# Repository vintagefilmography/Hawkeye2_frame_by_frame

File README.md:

# Hawkeye2_frame_by_frame
The purpose of this project is to prvide the instruction to the user on how to modify the existing 8mm film projector for the frame-byframe capture directly into the camera using a small MSP430 based board.  
Generally the projects of this type require several modifications to the projector including the light change, motor change and addition of some type of a trigger detector for the camera.  
This project also requires the light change and the motor change, but unlike similar other projects, it does not require the trigger mechanism. The trigger is pprovided by the MSP430 controller. The controller is programmed to precisely control the stepper motor rotation so that the film gets advanced exactly one frame at the time. The camera trigger is then generated at the end of frame advance.  

System Components

## Hawkeye2 Controller  
At the heart of the system is the Hawkeye2 controller. This is a custom design. All design info is available gere is this repository. The board details are included in  the homemade-v3 folder. Download the folder to your Eagle project directory and there you will have access to the schematic and the board layout. 
The MSP430 micro controller firmware is available in the MSP folder. Download the zip file from there and save it in you TI Code Composer project directory. From there you can edit the source and flash the target by using TI Launchpad.  
There are two more boards included. One is for the front panel switches and the other is for the switch interface board. Follow the included wiring diagram to interconnect the system.
## Stepper Driver  
The stepper driver is an off the shelf product. 
https://www.amazon.com/gp/product/B075HBJP51/
There are many other variants available. This particular one is a good choice because it has 256 micro steps allowing for a very precise tuning control. One disadvantage is that it operates from a 24VDC source so that 2 DC adaprers are required, one for the driver and the other one for the controller that requires 12VDC source.  
Driver dip switches  
The following is recommended:
SW4 - Half Currect
Current - 
1.4A for this type motor https://www.amazon.com/gp/product/B00PNEQKC0/
2.7A for this type motor https://www.amazon.com/gp/product/B00PNEPF5I/
Set the pulse/rev switches for the highest speed that can still hold the torque and there is no skipping of steps. Skipping will result in loss of synchronization.  
## Stepper Motor  
These two motors were tested.
1.4A for this type motor https://www.amazon.com/gp/product/B00PNEQKCdesigned with Spark0/
2.7A for this type motor https://www.amazon.com/gp/product/B00PNEPF5I/
You will have to design a bracket for the motor so that it fits properly in the projector after you remove the old motor. 
A sample stepper bracket is included here as a good staring point. Use the Designspark Mechanical free software to modify the bracket for your projector.

## Pulley
There are quite a few pulleys avaliable online.  
Example:  
https://www.amazon.com/gp/product/B07C4R3PGV/  
https://www.amazon.com/gp/product/B07C4QD1BV/
You can also design your own. A sample design will be included here shortly.

## Belt
This used to be a big problem but with the neophrene Urethane belting that became available it is easy to make your own custom belt.
https://www.amazon.com/gp/product/B07L3W7Z1N  
Follow the following instructions:  
https://www.youtube.com/watch?v=mBtHvPWVgDw

## Control Switches:

The control switches control the operation of the unit.  
### RUN Switch
Pauses the operation  
### ALIGN
Slowly advances the film until the frame is centered in the camera. Also turns tuning on if activated in run mode.  
### REW
Turns takeup continuously on if run switch is off.  
The switch can also be used in conjuction with the PROJ switch to select the projector type. 
I.e. if the setup is used with multiple projectors then the projector synchronization can be saved in non volatile memory.  
Four memory locations are available:   
REW     PROJ  
0       0       Projector1  
0       1       Projector2  
1       0       Projector3  
1       1       Projector4  
The switches are active only during a short time after the power is plugged in and in most cases the only Projector1 selection will be used.  

### PROJ 
Seects the projector type used. In most cases this switch will be kept off. 
The projector selection is read by the firmware upon board power up and cannot be changed after that during normal operation.  
### UP and DOWN switches 
Used during tuning mode to run change the length of stepper advance.  
### Up and DOWN buttons
Located on the controller board, used for fine tuning of the stepper  
### REV Switch 
Reverses the motor rotation for film rewind.  

## Operation
Very straight forward. Here is a short video showing the operation.  
https://photos.app.goo.gl/MLEgviiinpVREHCQA  
As the video shows, plug the power in for both the controller and the driver and then flip the ADV switch on until the projector is finished with the film frame advance and at that point turn the ADV switch off. Then, connect the camera trigger and turn the camera on. Turn the RUn switch on the the camera will start capturing the farmes. If at any point the system starts goung out of sync you can resync it by using the ADV switch or alternatively, turn the ALG switch on and the hit the UP or DOWN button just once.   
The UP button makes the run shorter and the DOWN button makes it longer.  

## Tuning the Stepper  
Turn the RUN switch on. Make sure all other switches are off.

Turn the ALIGN switch on.  
This puts the controller into tuning mode.  
Turn on the DOWN switch. This makes the stepper step one count longer.  
While the DOWN switch is still on, turn on the UP switch.  
This will cause continuous stepper count increase. You will see that the film advance becomes larger and larger.   
After a while the stepper motor advance will  be close to one full turn of the projector cam.  
Once the alignment is close to a full cam rotation, turn the UP switch off and then the DOWN switch off.   
Continue with fine tuning by using the controller board mounted UP and DOWN buttons.  
The UP button will make the advance shorter by one count and conversely, the DOWN button will make it longer by one count.  
Once the alignment is done DO NOT POWER THE BOARD DOWN.  
Turn the ALIGN switch off and then the RUN switch off. Then you can power the board down.  
Power the board up again with the correct memory selected.
Turn the RUN switch on and check that the alignment was restored properly from the memory.  
It is to be noted that the UP and DOWN sequence can be reversed if the Film advance is too large.  
In that case turn the UP switch on first followed by the DOWN switch.   
Once done, turn the DOWN switch off first followed by the UP switch.

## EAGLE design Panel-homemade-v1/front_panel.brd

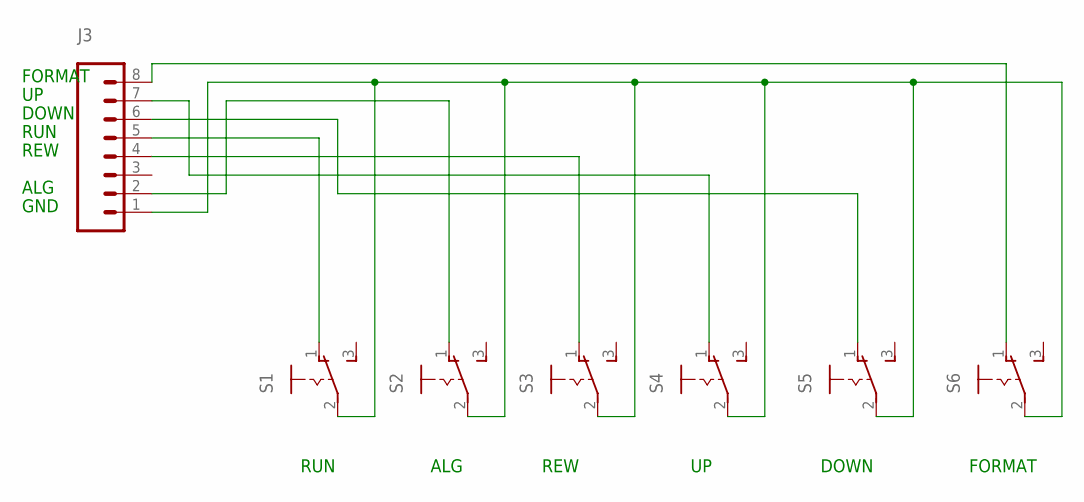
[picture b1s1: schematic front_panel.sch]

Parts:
J3: CONN_08"; 1X08
S1, S2, S3, S4, S5, S6: M251

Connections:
unnamed: J3.1, S1.2, S2.2, S3.2, S4.2, S5.2, S6.2
unnamed: J3.6, S5.1 (O)
unnamed: J3.4, S3.1 (O)
unnamed: J3.7, S4.1 (O)
unnamed: J3.2, S2.1 (O)
unnamed: J3.5, S1.1 (O)
unnamed: J3.8, S6.1 (O)

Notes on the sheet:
GND
ALG
REW
RUN
DOWN
FORMAT

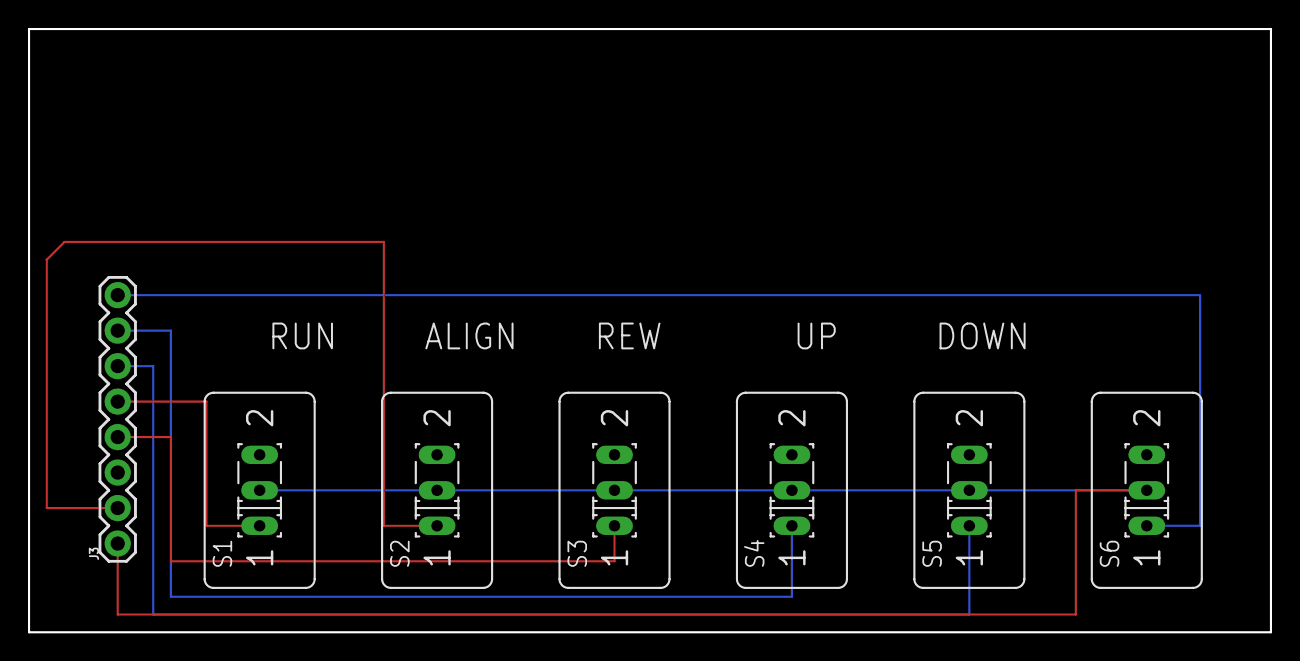
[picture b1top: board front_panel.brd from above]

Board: 2 copper layers, 88.9 x 43.2 mm, 7 parts (0 on the bottom side), 7 nets.

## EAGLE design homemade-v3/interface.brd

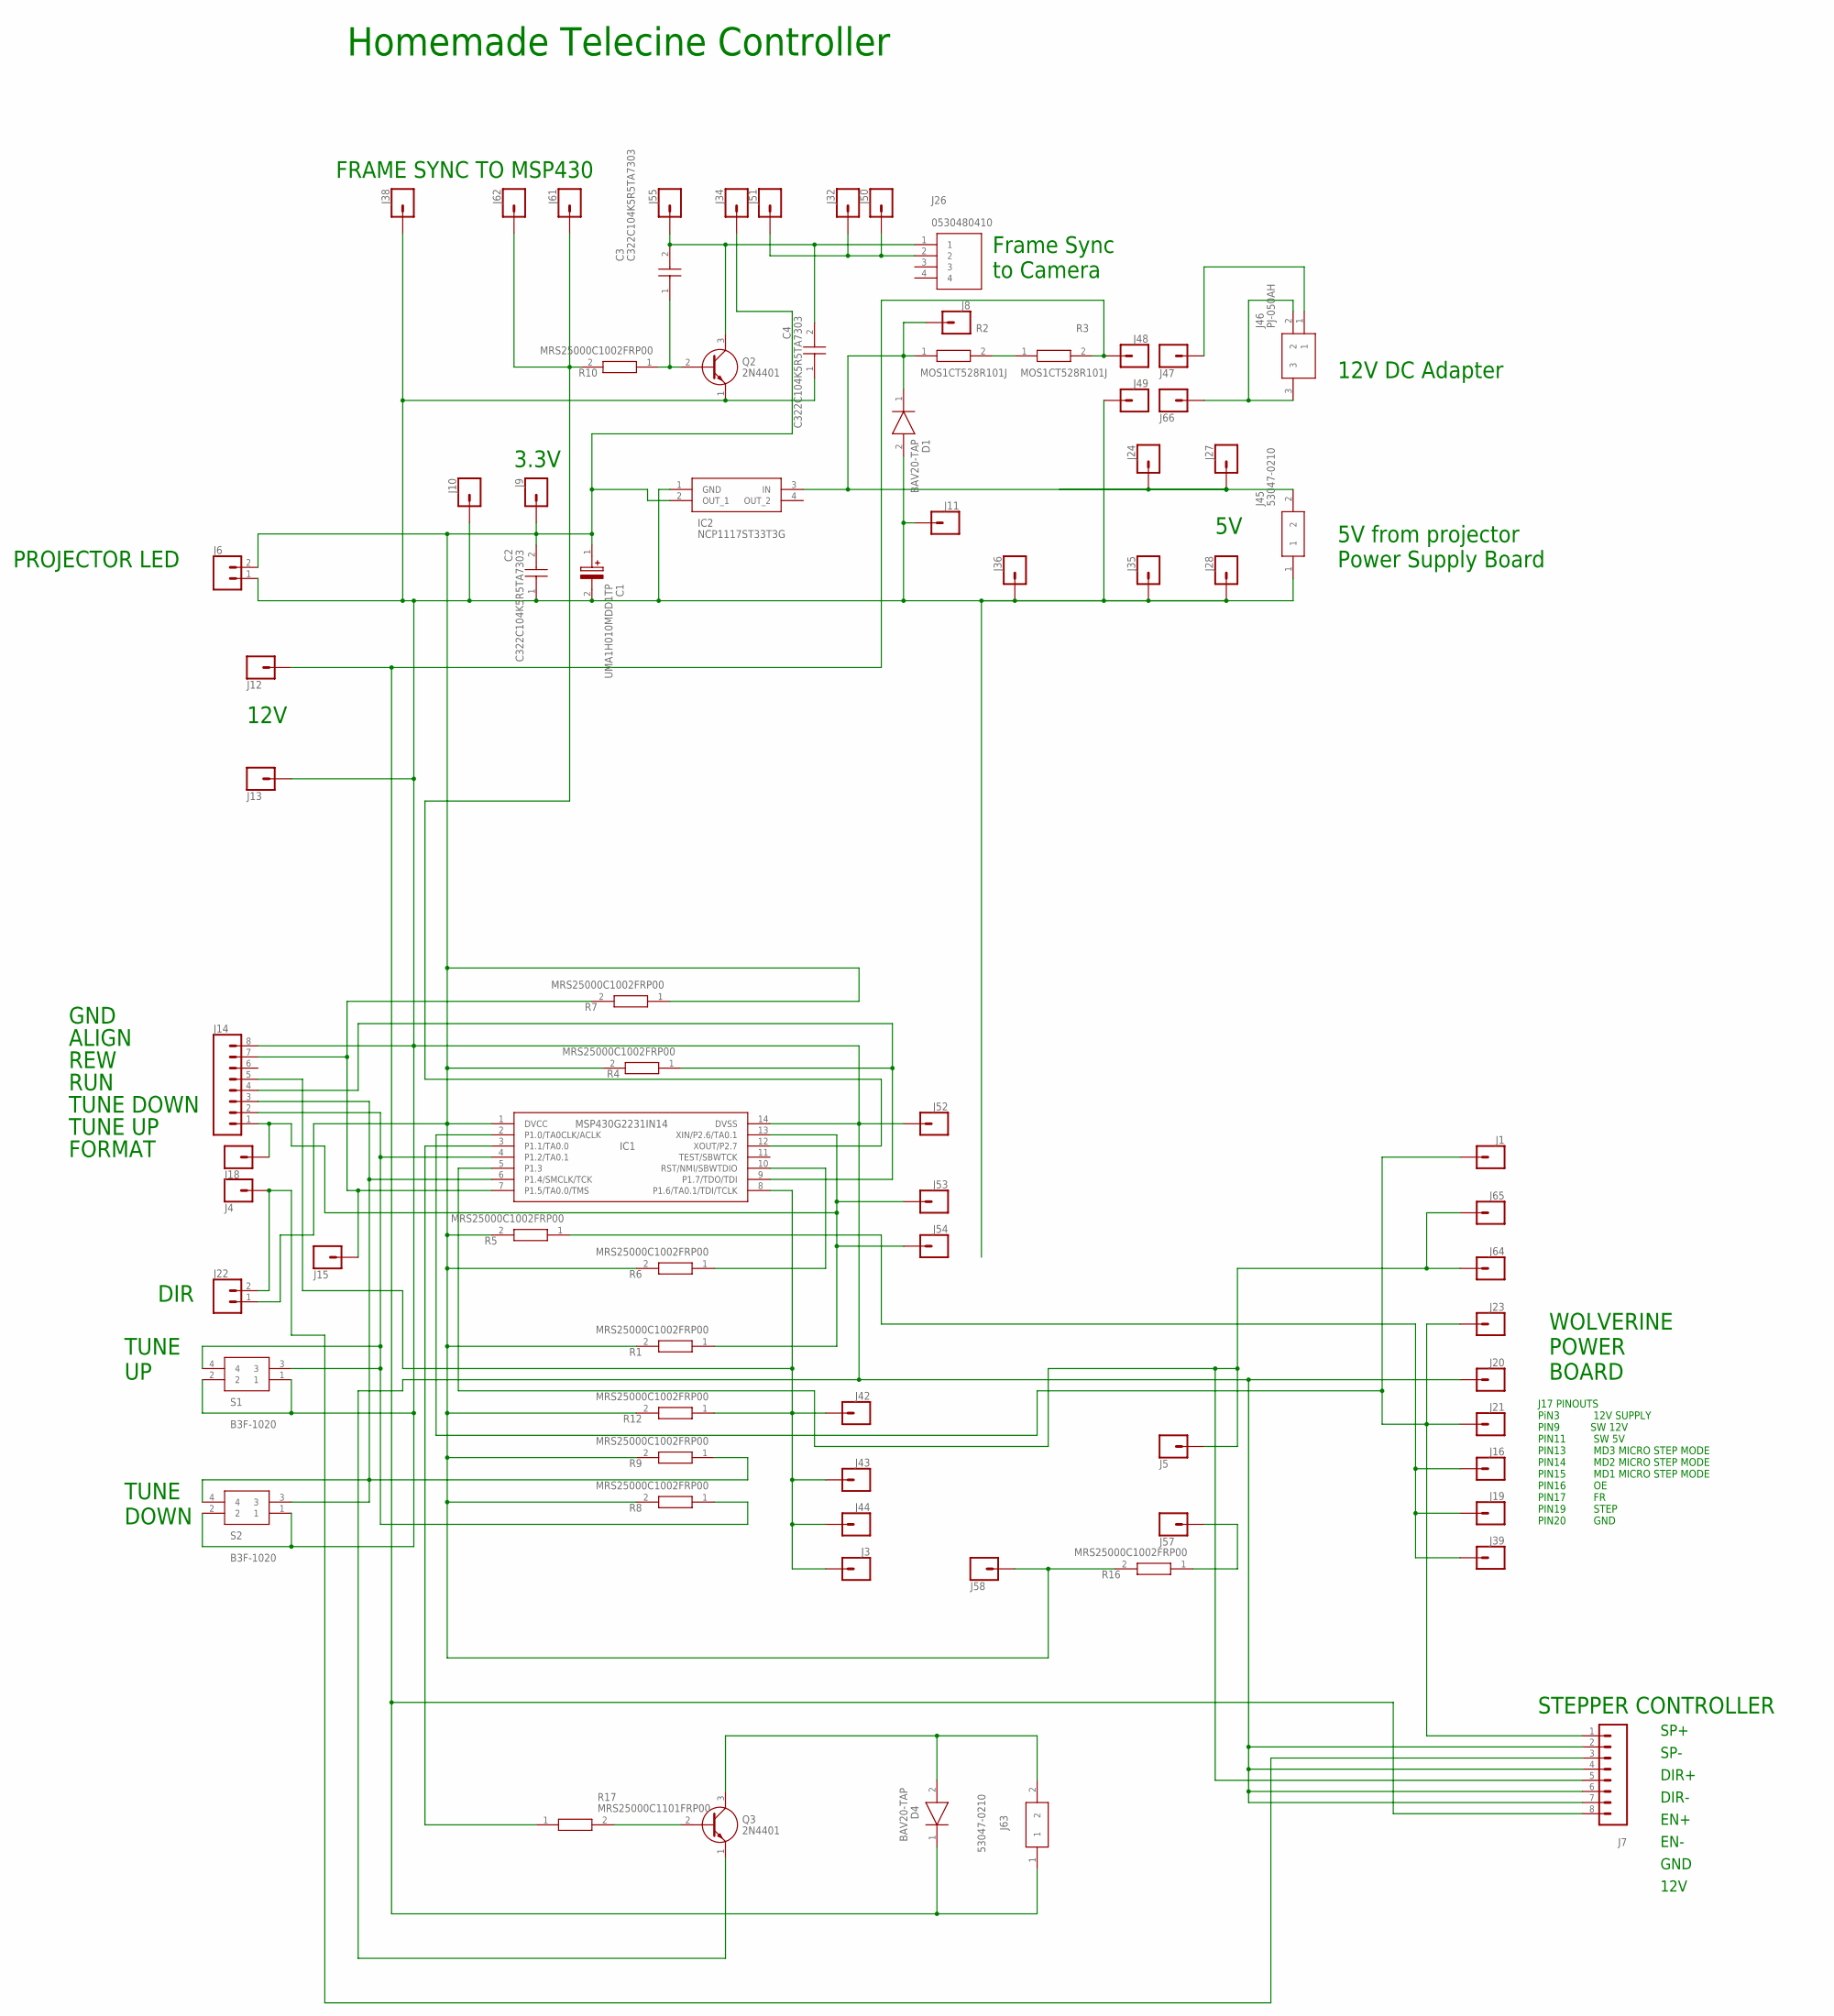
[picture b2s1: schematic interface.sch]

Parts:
C1: UMA1H010MDD1TP; CAPPRD150W45D450H600
C2, C3, C4: C322C104K5R5TA7303; C322
D1, D4: BAV20-TAP; DIOAD950W60L350D150
IC1: MSP430G2231IN14; DIP254P762X508-14
IC2: NCP1117ST33T3G; SOT230P700X180-4N
J1, J3, J4, J5, J8, J9, J10, J11, J12, J13, J15, J16, J18, J19, J20, J21, J23, J24, J27, J28, J32, J34, J35, J36, J38, J39, J42, J43, J44, J47, J48, J49, J50, J51, J52, J53, J54, J55, J57, J58, J61, J62, J64, J65, J66: CONN_01; 1X01
J6, J22: CONN_02; 1X02
J7, J14: CONN_08"; 1X08
J26: 0530480410; SHDR4W35P0X125_1X4_675X550X350
J45, J63: 53047-0210
J46: PJ-050AH; PJ050AH
Q2, Q3: 2N4401; CS_TO-92
R1, R4, R5, R6, R7, R8, R9, R10, R12, R16: MRS25000C1002FRP00; RESAD1650W60L650D250
R2, R3: MOS1CT528R101J; RESAD2100W60L900D300
R17: MRS25000C1101FRP00; RESAD1650W60L650D250
S1, S2: B3F-1020; B3F1000

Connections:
unnamed: C3.2, C4.2, J26.1, J55.1, Q2.3 (C)
unnamed: IC1.13 (XIN/P2.6/TA0.1), J14.1, J18.1, J53.1, J54.1, R1.1
unnamed: D4.1 (K), J7.8, J12.1, J48.1, J63.1, R3.2
unnamed: IC1.9 (P1.7/TDO/TDI), J14.4, R4.1
unnamed: J57.1, R16.1
unnamed: C1.1 (+), C2.2, IC1.1 (DVCC), IC2.2 (OUT_1), J6.2, J9.1, J22.1, J34.1, J58.1, R1.2, R4.2, R5.2, R6.2, R7.1, R8.2, R9.2, R12.2, R16.2
unnamed: IC1.3 (P1.1/TA0.0), R17.1
unnamed: IC1.10 (RST/NMI/SBWTDIO), R6.1
unnamed: R2.2, R3.1
unnamed: J4.1, J7.3, J22.2
unnamed: D1.1 (K), IC2.3 (IN), J8.1, J24.1, J27.1, J45.2, R2.1
unnamed: J46.1, J47.1
unnamed: IC1.7 (P1.5/TA0.0/TMS), J14.7, J15.1, R7.2
unnamed: J16.1, J19.1, J39.1, R5.1
unnamed: IC1.5 (P1.3), J5.1, J7.5, J64.1, J65.1
unnamed: IC1.2 (P1.0/TA0CLK/ACLK), J1.1, J7.1, J21.1, J23.1
unnamed: IC1.4 (P1.2/TA0.1), J14.2, R8.1, S1.3, S1.4
unnamed: C1.2 (-), C2.1, C4.1, D1.2 (A), IC1.14 (DVSS), IC2.1 (GND), J6.1, J7.2, J7.4, J7.6, J7.7, J10.1, J11.1, J13.1, J14.8, J20.1, J28.1, J35.1, J36.1, J38.1, J45.1, J49.1, J52.1, Q2.1 (E), Q3.1 (E), S1.1, S1.2, S2.1, S2.2
unnamed: IC1.6 (P1.4/SMCLK/TCK), J14.3, R9.1, S2.3, S2.4
unnamed: IC1.12 (XOUT/P2.7), J61.1, J62.1, R10.2
unnamed: Q3.2 (B), R17.2
unnamed: C3.1, Q2.2 (B), R10.1
unnamed: J26.2, J32.1, J50.1, J51.1
unnamed: IC1.8 (P1.6/TA0.1/TDI/TCLK), J3.1, J14.5, J42.1, J43.1, J44.1, R12.1
unnamed: J46.2, J46.3, J66.1
unnamed: D4.2 (A), J63.2, Q3.3 (C)

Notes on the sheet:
Homemade Telecine Controller
PROJECTOR LED
3.3V
FRAME SYNC TO MSP430
Frame Sync to Camera
5V from projector Power Supply Board
12V
RUN
ALIGN
WOLVERINE POWER BOARD
J17 PINOUTS PiN3 12V SUPPLY PIN9 SW 12V PIN11 SW 5V PIN13 MD3 MICRO STEP MODE PIN14 MD2 MICRO STEP MODE PIN15 MD1 MICRO STEP MODE PIN16 OE PIN17 FR PIN19 STEP PIN20 GND
12V DC Adapter
SP-
STEPPER CONTROLLER
SP+
EN-
EN+
DIR-
DIR+
GND
REW
DIR
TUNE UP
TUNE DOWN
TUNE DOWN
TUNE UP
FORMAT

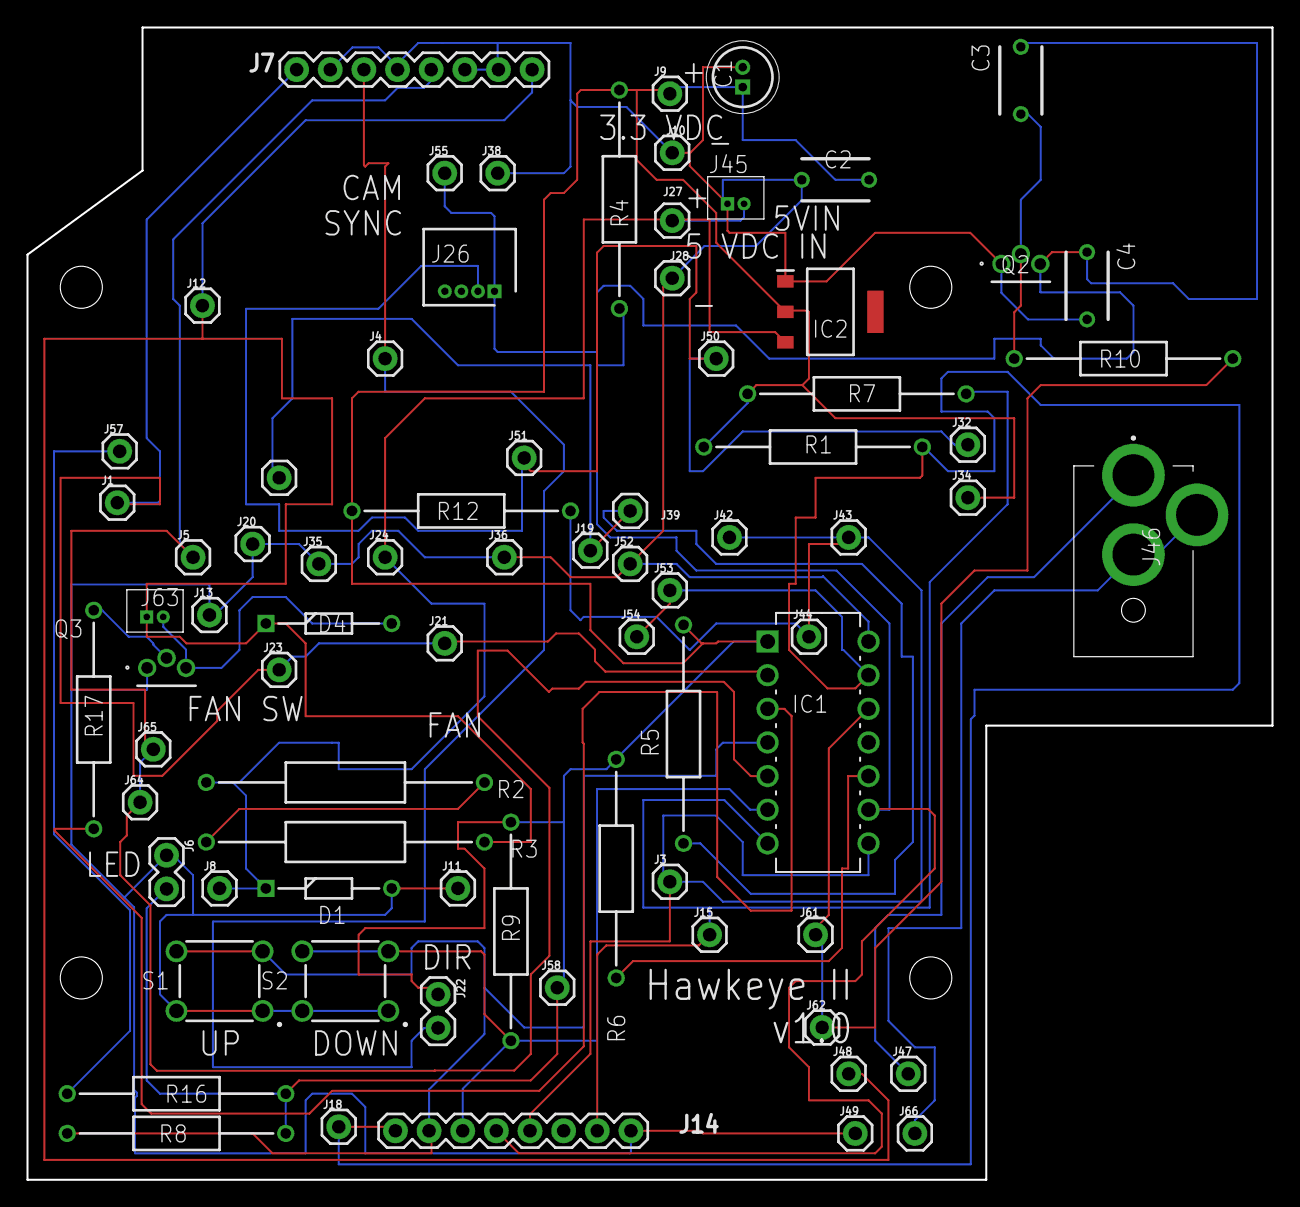
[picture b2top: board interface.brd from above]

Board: 2 copper layers, 94.0 x 87.0 mm, 78 parts (0 on the bottom side), 26 nets.

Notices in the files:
parts and their libraries:
SparkFun-Connectors: Licensing: Creative Commons ShareAlike 4.0 International - https://creativecommons.org/licenses/by-sa/4.0
